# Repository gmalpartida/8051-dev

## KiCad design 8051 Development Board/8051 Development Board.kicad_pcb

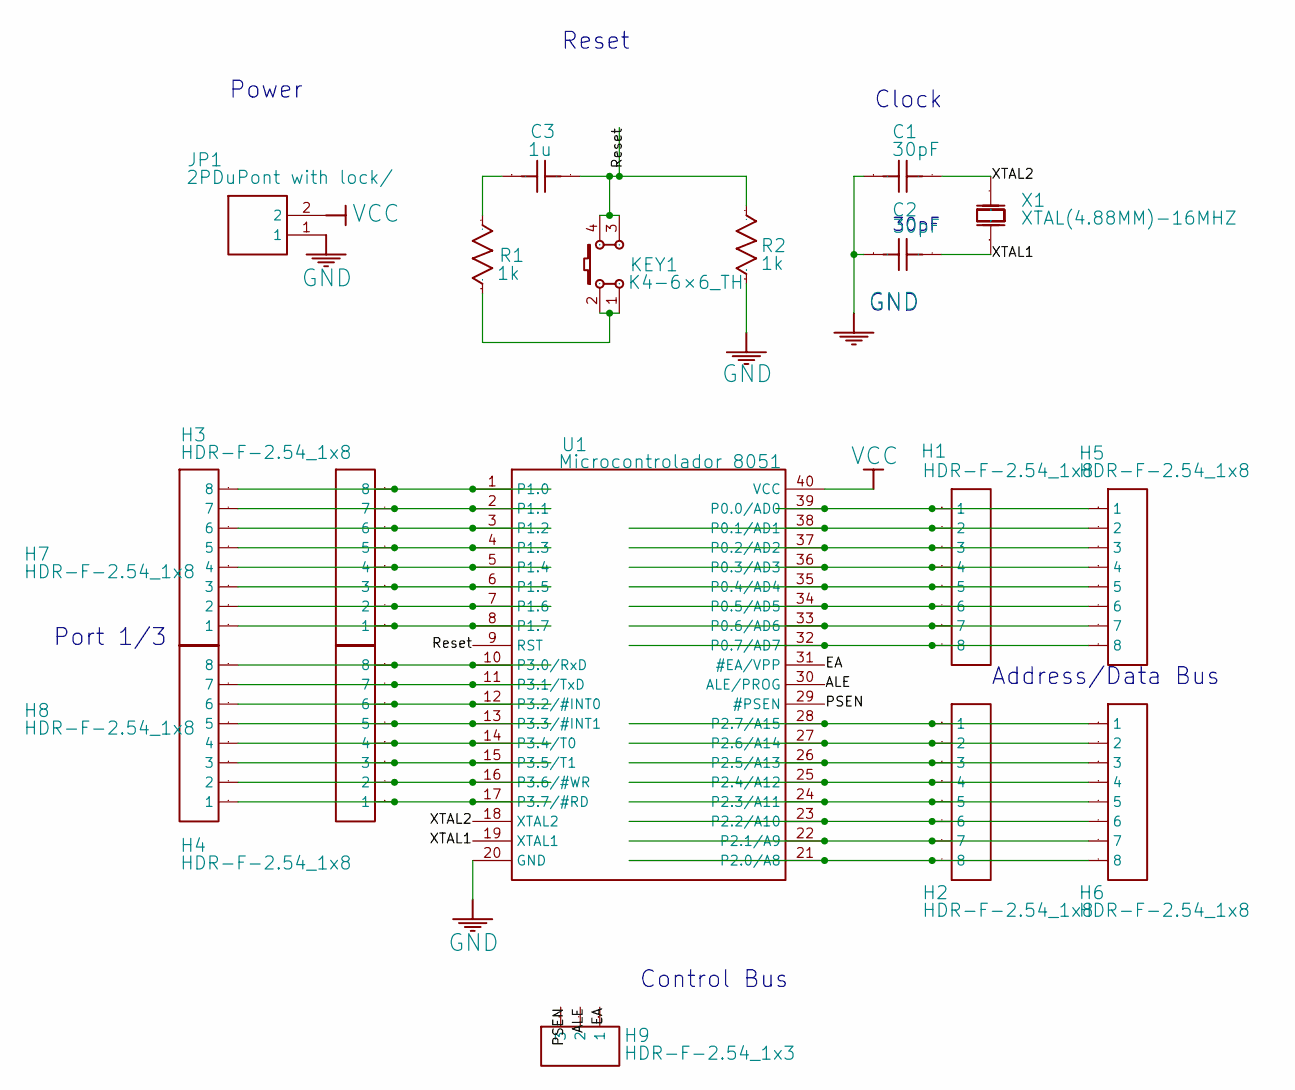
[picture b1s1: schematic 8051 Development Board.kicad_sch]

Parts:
C1, C2: 30pF; Manufacturer Part CC4-0805-CG-50V-30pF-J
C3: 1u
H1, H2, H3, H4, H5, H6, H7, H8: HDR-F-2.54_1x8
H9: HDR-F-2.54_1x3
JP1: 2PDuPont with lock/; Manufacturer Part 杜邦2.54-2AS
KEY1: K4-6×6_TH; Manufacturer Part K2-1102DP-E4SW-04
R1, R2: 1k
U1: Microcontrolador 8051; Manufacturer Part Microcontrolador
X1: XTAL(4.88MM)-16MHZ; Manufacturer Part XTAL(4.88MM)-16MHz

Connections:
ALE: H9.2, U1.30 (ALE/PROG)
C3_1: C3.1, R1.2
EA: H9.1, U1.31 (#EA/VPP)
GND: C1.1, C2.1, JP1.1, R2.1, U1.20 (GND)
KEY1_1: KEY1.1, KEY1.2, R1.1
PSEN: H9.3, U1.29 (#PSEN)
RESET: C3.2, KEY1.3, KEY1.4, R2.2, U1.9 (RST)
U1_1: H3.8, H7.8, U1.1 (P1.0)
U1_2: H3.7, H7.7, U1.2 (P1.1)
U1_3: H3.6, H7.6, U1.3 (P1.2)
U1_4: H3.5, H7.5, U1.4 (P1.3)
U1_5: H3.4, H7.4, U1.5 (P1.4)
U1_6: H3.3, H7.3, U1.6 (P1.5)
U1_7: H3.2, H7.2, U1.7 (P1.6)
U1_8: H3.1, H7.1, U1.8 (P1.7)
U1_10: H4.8, H8.8, U1.10 (P3.0/RxD)
U1_11: H4.7, H8.7, U1.11 (P3.1/TxD)
U1_12: H4.6, H8.6, U1.12 (P3.2/#INT0)
U1_13: H4.5, H8.5, U1.13 (P3.3/#INT1)
U1_14: H4.4, H8.4, U1.14 (P3.4/T0)
U1_15: H4.3, H8.3, U1.15 (P3.5/T1)
U1_16: H4.2, H8.2, U1.16 (P3.6/#WR)
U1_17: H4.1, H8.1, U1.17 (P3.7/#RD)
U1_21: H2.8, H6.8, U1.21 (P2.0/A8)
U1_22: H2.7, H6.7, U1.22 (P2.1/A9)
U1_23: H2.6, H6.6, U1.23 (P2.2/A10)
U1_24: H2.5, H6.5, U1.24 (P2.3/A11)
U1_25: H2.4, H6.4, U1.25 (P2.4/A12)
U1_26: H2.3, H6.3, U1.26 (P2.5/A13)
U1_27: H2.2, H6.2, U1.27 (P2.6/A14)
U1_28: H2.1, H6.1, U1.28 (P2.7/A15)
U1_32: H1.8, H5.8, U1.32 (P0.7/AD7)
U1_33: H1.7, H5.7, U1.33 (P0.6/AD6)
U1_34: H1.6, H5.6, U1.34 (P0.5/AD5)
U1_35: H1.5, H5.5, U1.35 (P0.4/AD4)
U1_36: H1.4, H5.4, U1.36 (P0.3/AD3)
U1_37: H1.3, H5.3, U1.37 (P0.2/AD2)
U1_38: H1.2, H5.2, U1.38 (P0.1/AD1)
U1_39: H1.1, H5.1, U1.39 (P0.0/AD0)
VCC: JP1.2, U1.40 (VCC)
XTAL1: C2.2, U1.19 (XTAL1), X1.1 (OSC1)
XTAL2: C1.2, U1.18 (XTAL2), X1.2 (OSC2)

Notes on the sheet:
Control Bus
GND
Address/Data Bus
Power
Port 1/3
Reset
30pF
Clock

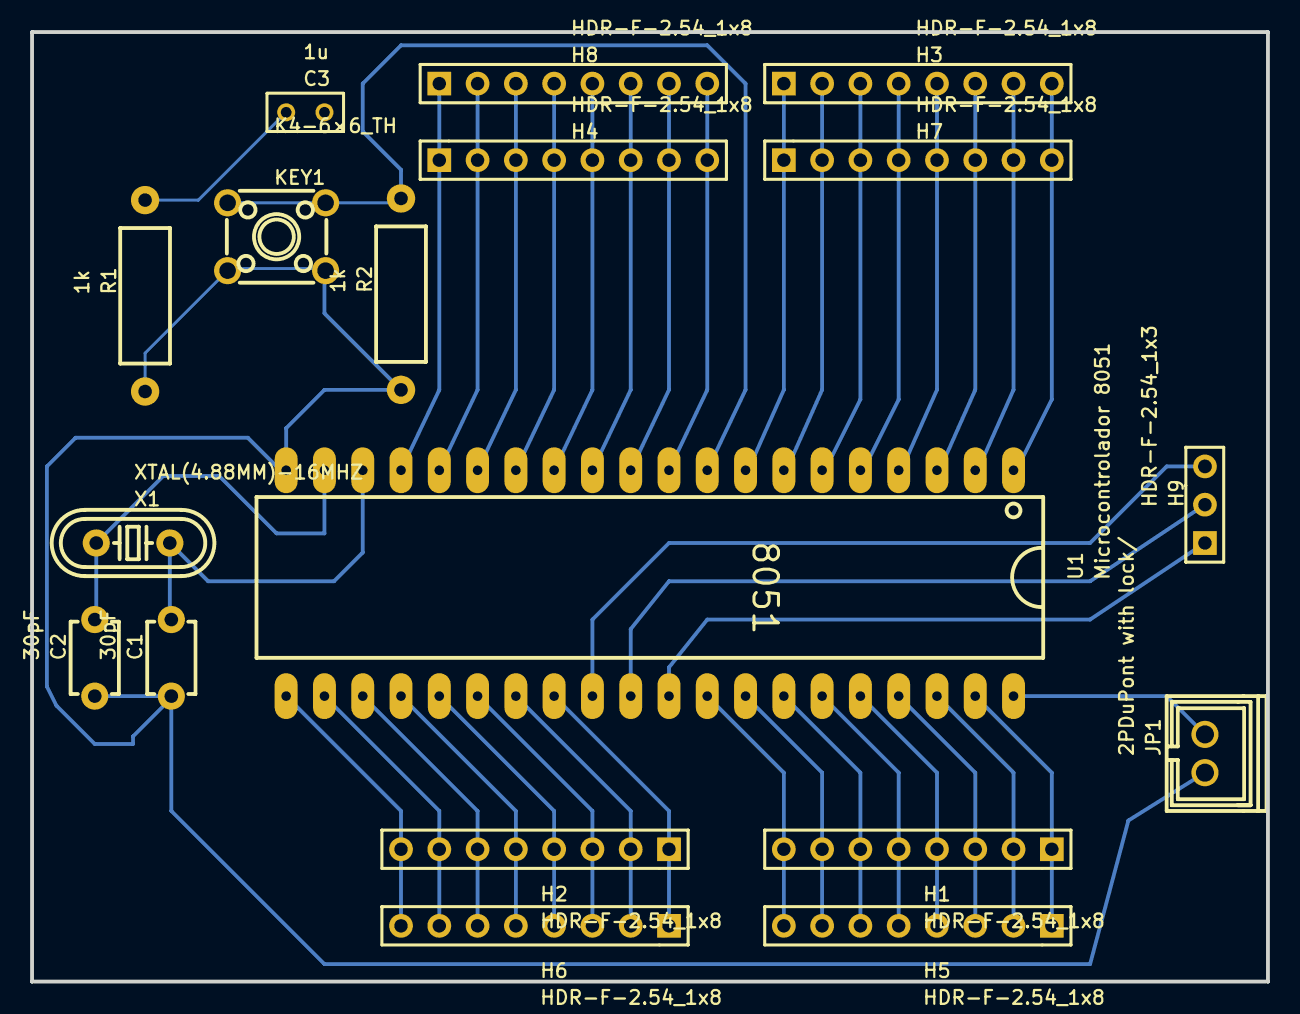
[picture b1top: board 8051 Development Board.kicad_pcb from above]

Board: 2 copper layers, 82.0 x 63.0 mm, 18 parts (0 on the bottom side), 42 nets.

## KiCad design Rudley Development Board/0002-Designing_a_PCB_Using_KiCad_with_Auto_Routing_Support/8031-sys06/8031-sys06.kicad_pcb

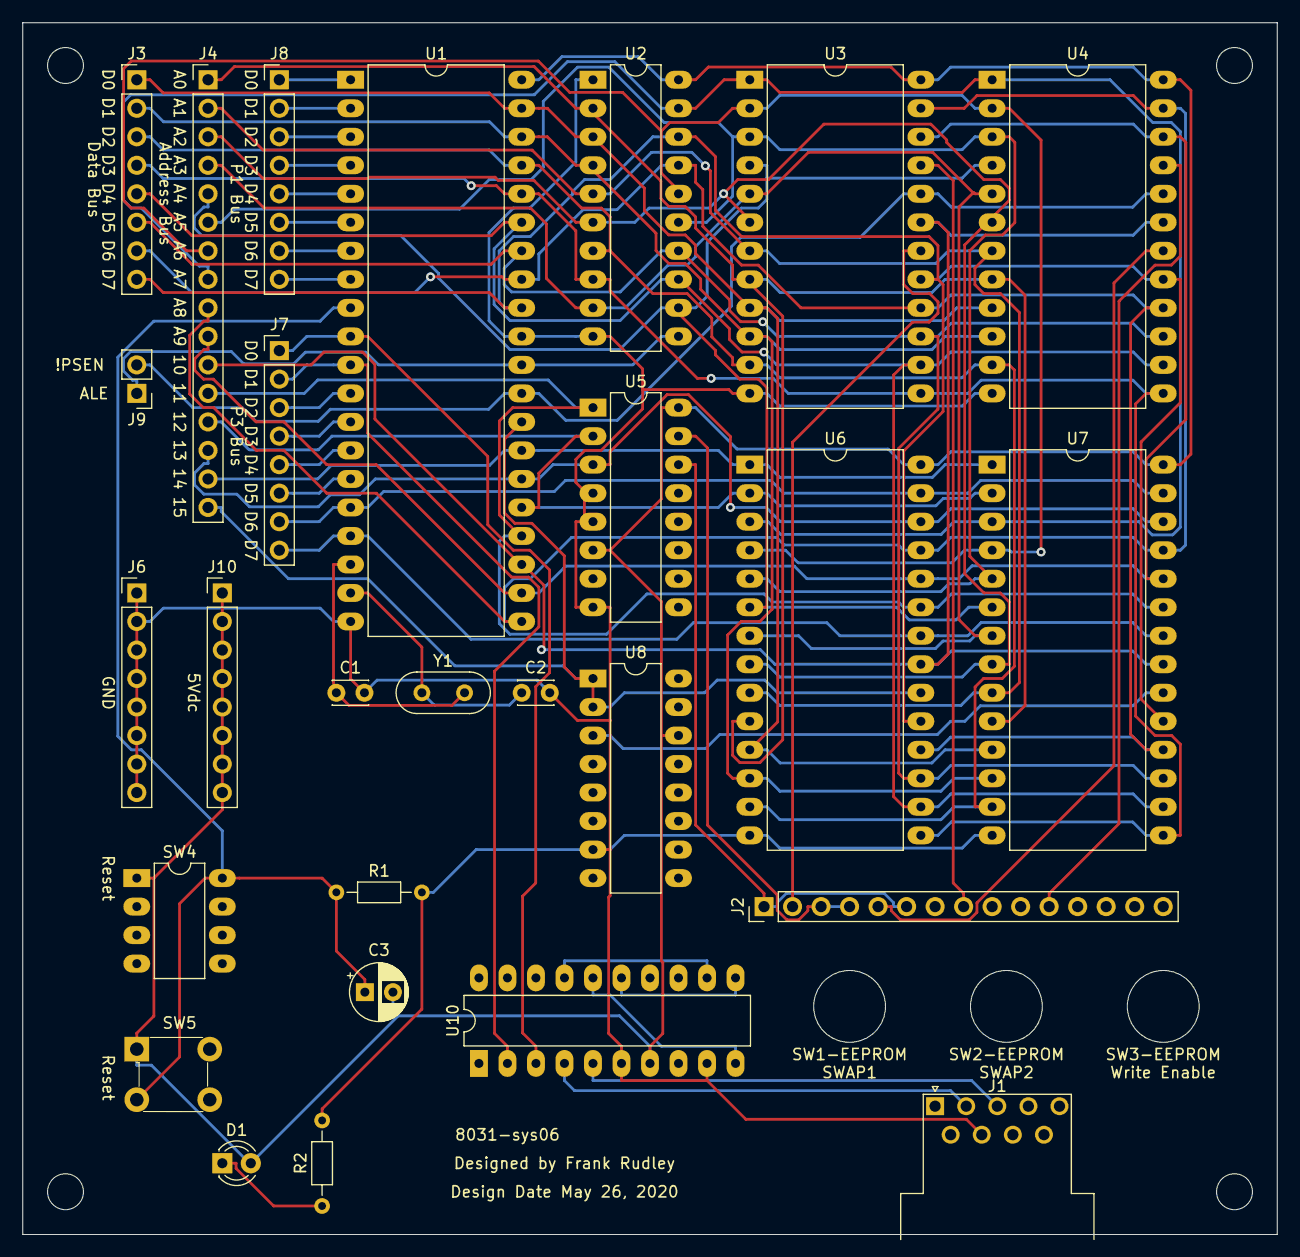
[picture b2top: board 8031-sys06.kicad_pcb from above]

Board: 2 copper layers, 111.8 x 108.0 mm, 34 parts (0 on the bottom side), 60 nets.

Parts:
C1, C2: 30pf; C_Disc_D3.0mm_W2.0mm_P2.50mm
C3: 10uf; CP_Radial_D5.0mm_P2.50mm
D1: LED; LED_D3.0mm
J1: RS232; DSUB-9_Male_Horizontal_P2.77x2.54mm_EdgePinOffset9.40mm
J2: Switches; PinHeader_1x15_P2.54mm_Vertical
J3: Data Bus; PinHeader_1x08_P2.54mm_Vertical
J4: Address Bus; PinHeader_1x16_P2.54mm_Vertical
J6: GND Bus; PinHeader_1x08_P2.54mm_Vertical
J7: P3 Bus; PinHeader_1x08_P2.54mm_Vertical
J8: P1 Bus; PinHeader_1x08_P2.54mm_Vertical
J9: CNTL Bus; PinHeader_1x02_P2.54mm_Vertical
J10: 5V Bus; PinHeader_1x08_P2.54mm_Vertical
R1: 8.2K; R_Axial_DIN0204_L3.6mm_D1.6mm_P7.62mm_Horizontal
R2: 220; R_Axial_DIN0204_L3.6mm_D1.6mm_P7.62mm_Horizontal
REF1, REF2, REF3, REF4: MountingHole_3.2mm_M3
REF5, REF6, REF7: MountingHole_6.4mm_M6
SW4: SW_DIP_x04; DIP-8_W7.62mm_LongPads
SW5: Reset; Switch_Tactile_THT_6x6mm
U1: 8031; DIP-40_W15.24mm_LongPads
U2: 74LS373; DIP-20_W7.62mm_LongPads
U3, U4: AT28C16; DIP-24_W15.24mm_LongPads
U5: 74LS138; DIP-16_W7.62mm_LongPads
U6, U7: 62C256; DIP-28_W15.24mm_LongPads
U8: 74LS00; DIP-16_W7.62mm_LongPads
U10: MAX233; DIP-20_W7.62mm_LongPads
Y1: 11.059MHz; Crystal_HC52-6mm_Vertical

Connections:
!CS: J4.16, U1.28, U6.20, U8.1, U8.2
!INT0: J7.3, U1.12
!INT1: J7.4, U1.13
!OE: J7.8, U1.17, U6.22, U7.22
!WE: J7.7, U1.16, U6.27, U7.27
+5V: C3.2, D1.2, J10.1, J10.2, J10.3, J10.4, J10.5, J10.6, J10.7, J10.8, SW4.1, SW5.1, U1.40, U2.20, U3.24, U4.24, U5.6, U5.16, U6.28, U7.28, U8.14, U10.7
/A0: J4.1, U2.2, U3.8, U4.8, U6.10, U7.10
/A1: J4.2, U2.5, U3.7, U4.7, U6.9, U7.9
/A2: J4.3, U2.6, U3.6, U4.6, U6.8, U7.8
/A3: J4.4, U2.9, U3.5, U4.5, U6.7, U7.7
/A4: J4.5, U2.12, U3.4, U4.4, U6.6, U7.6
/A5: J4.6, U2.15, U3.3, U4.3, U6.5, U7.5
/A6: J4.7, U2.16, U3.2, U4.2, U6.4, U7.4
/A7: J4.8, U2.19, U3.1, U4.1, U6.3, U7.3
/A8: J4.9, U1.21, U3.23, U4.23, U6.25, U7.25
/A9: J4.10, U1.22, U3.22, U4.22, U6.24, U7.24
/A10: J4.11, U1.23, U3.19, U4.19, U6.21, U7.21
/A11: J4.12, U1.24, U5.1, U6.23, U7.23
/A12: J4.13, U1.25, U5.2, U6.2, U7.2
/A13: J4.14, U1.26, U5.3, U6.26, U7.26
/A14: J4.15, U1.27, U6.1, U7.1
/D0: J3.1, U1.39, U2.3, U3.9, U4.9, U6.11, U7.11
/D1: J3.2, U1.38, U2.4, U3.10, U4.10, U6.12, U7.12
/D2: J3.3, U1.37, U2.7, U3.11, U4.11, U6.13, U7.13
/D3: J3.4, U1.36, U2.8, U3.13, U4.13, U6.15, U7.15
/D4: J3.5, U1.35, U2.13, U3.14, U4.14, U6.16, U7.16
/D5: J3.6, U1.34, U2.14, U3.15, U4.15, U6.17, U7.17
/D6: J3.7, U1.33, U2.17, U3.16, U4.16, U6.18, U7.18
/D7: J3.8, U1.32, U2.18, U3.17, U4.17, U6.19, U7.19
GND: C1.2, C2.2, J1.7, J6.1, J6.2, J6.3, J6.4, J6.5, J6.6, J6.7, J6.8, R1.2, R2.2, U1.20, U1.31, U2.1, U2.10, U3.12, U4.12, U5.4, U5.5, U5.8, U6.14, U7.14, U8.7, U10.6, U10.9
unnamed: C1.1, U1.18, Y1.2
unnamed: C2.1, U1.19, Y1.1
unnamed: C3.1, R1.1, SW4.8, SW5.3, U1.9
unnamed: D1.1, R2.1
unnamed: J1.2, U10.4
unnamed: J1.3, U10.5
unnamed: J2.1, J2.6, U5.14
unnamed: J2.2, U3.18
unnamed: J2.3, J2.4, U5.15
unnamed: J2.5, U4.18
unnamed: J2.8, U3.21
unnamed: J2.11, U4.21
unnamed: J8.1, U1.1
unnamed: J8.2, U1.2
unnamed: J8.3, U1.3
unnamed: J8.4, U1.4
unnamed: J8.5, U1.5
unnamed: J8.6, U1.6
unnamed: J8.7, U1.7
unnamed: J8.8, U1.8
unnamed: J9.1, U1.30, U2.11
unnamed: J9.2, U1.29, U3.20, U4.20
unnamed: U7.20, U8.3
unnamed: U10.10, U10.16
unnamed: U10.11, U10.15
unnamed: U10.12, U10.17
RXD: J7.1, U1.10, U10.3
T0: J7.5, U1.14
T1: J7.6, U1.15
TXD: J7.2, U1.11, U10.2

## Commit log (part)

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2025-10-13 added uart_rx_char and uart_tx_char
2025-10-14 implement menu.asm
2025-10-16 added get_cmd function
2025-10-17 added command handling
2025-10-19 fix Makefile for mem_test
2025-10-23 compile blink_led2
2025-10-25 added verify function
2025-10-25 added .gitignore
2025-10-26 added mem_diag
2025-11-01 added basic manual
2025-11-01 added mem_test app
2025-11-02 change monitor to start user programs at 0x8000
2025-11-06 added logo
2025-11-16 added asc2bin function
2025-11-16 recent changes
2025-11-23 added test_port1 program
2025-11-24 removed untracked files according to .gitignore
2025-11-24 acey-ducey fixed
2026-01-04 added basic commands: peek, poke, dump, clear, ls
2026-02-09 added more functions to monitor
2026-02-22 added move, fill, copy functions
2026-02-24 implemented help table, command table
2026-02-25 implement sfr command
2026-03-04 added do_iram function
2026-03-22 move programs to projects
2026-06-04 added tags file
2026-06-04 remove tags file
2026-06-11 added tags to .gitignore)
